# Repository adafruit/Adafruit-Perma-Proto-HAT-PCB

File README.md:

# Adafruit Perma-Proto HAT for Raspberry Pi Computers

&nbsp; <br />
Click to purchase from the Adafruit Shop:
- [With EEPROM](https://www.adafruit.com/product/2314)
- [Without EEPROM](https://www.adafruit.com/product/2310)

PCB files for the Adafruit Perma-Proto HAT for Raspberry Pi Computers (all with the 40 pin header)

Design your own Pi HAT, attach custom circuitry and otherwise dress your Pi Zero, A+, B+, Pi 2 or Pi 3 (any Pi with a 2x20 connector) with this jaunty prototyping HAT kit.

To kick off the Adafruit HAT party, we have this Perma-Proto inspired plug in daughter board. It has a grid of 0.1" prototyping soldering holes for attaching chips, resistors, LED, potentiometers and more. The holes are connected underneath with traces to mimic the solderless breadboards with which you're familiar. There's also long power strips for +3V, +5V and Ground connections to the Pi. Near the top we break out nearly every pin you could want to connect to the Pi (#26 didn't quite make the cut).

This is just the basic version of our Perma-Proto HAT.  It comes with a printed circuit board and a single 2x20 GPIO Header for Raspberry Pi to put your Perma-Proto on top of your Raspberry Pi (like a nice little hat...) This version does not come with an EEPROM so you can 'stack' it with other HATs without worrying about an EEPROM address collision.

Format is EagleCAD schematic and board layout

For more details, check out the product pages at

-----> https://www.adafruit.com/products/2310

-----> https://www.adafruit.com/products/2314

### License

Adafruit invests time and resources providing this open source design, please support Adafruit and open-source hardware by [purchasing products from Adafruit](https://www.adafruit.com)!

All text above must be included in any redistribution

Designed by Limor Fried/Ladyada for Adafruit Industries.
Creative Commons Attribution/Share-Alike, all text above must be included in any redistribution 
See license.txt for additional information.

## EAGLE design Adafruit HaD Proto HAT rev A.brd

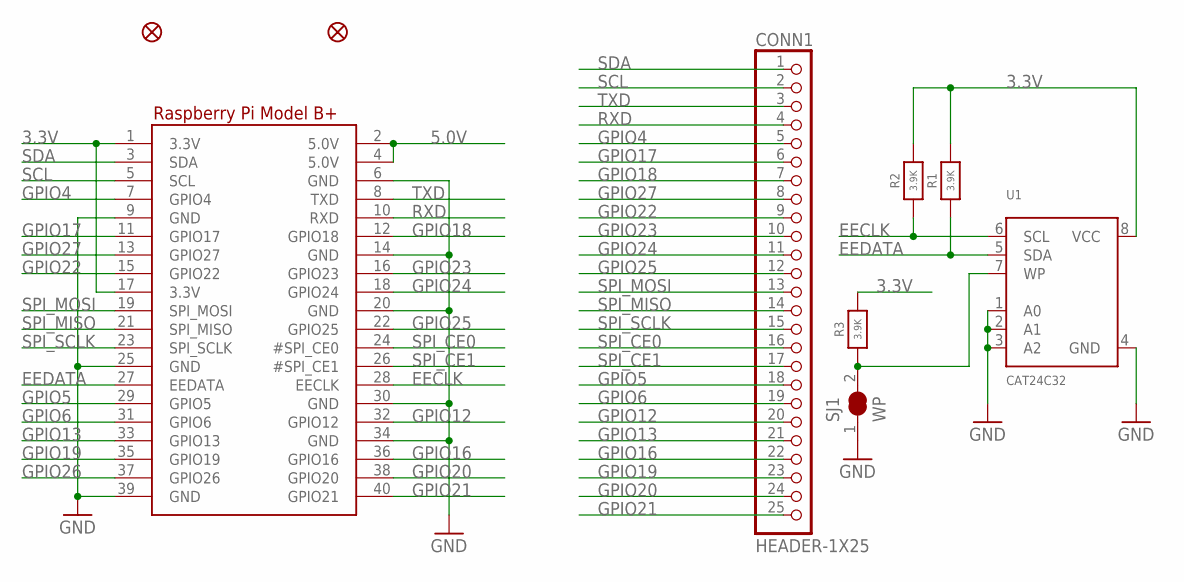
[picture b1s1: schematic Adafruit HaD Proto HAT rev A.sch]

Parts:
CONN1: HEADER-1X25; 1X25_ROUND_70MIL
FID2, FID3: FIDUCIAL""; FIDUCIAL_1MM
R1, R2, R3: 3.9K; 0805-NO
RPI1: RASPBERRYPI_BPLUS_HATNOSLOTS; PI_HAT_NOSLOTS
SJ1: WP; SOLDERJUMPER_CLOSEDWIRE
U1: CAT24C32; SOIC8_150MIL

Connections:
3.3V: R1.2, R2.2, R3.2, RPI1.1 (3.3V), RPI1.17 (3.3V), U1.8 (VCC)
5.0V: RPI1.2 (5.0V), RPI1.4 (5.0V)
EECLK: R2.1, RPI1.28 (EECLK), U1.6 (SCL)
EEDATA: R1.1, RPI1.27 (EEDATA), U1.5 (SDA)
GND: RPI1.6 (GND), RPI1.9 (GND), RPI1.14 (GND), RPI1.20 (GND), RPI1.25 (GND), RPI1.30 (GND), RPI1.34 (GND), RPI1.39 (GND), SJ1.1, U1.1 (A0), U1.2 (A1), U1.3 (A2), U1.4 (GND)
GPIO4: CONN1.5, RPI1.7 (GPIO4)
GPIO5: CONN1.18, RPI1.29 (GPIO5)
GPIO6: CONN1.19, RPI1.31 (GPIO6)
GPIO12: CONN1.20, RPI1.32 (GPIO12)
GPIO13: CONN1.21, RPI1.33 (GPIO13)
GPIO16: CONN1.22, RPI1.36 (GPIO16)
GPIO17: CONN1.6, RPI1.11 (GPIO17)
GPIO18: CONN1.7, RPI1.12 (GPIO18)
GPIO19: CONN1.23, RPI1.35 (GPIO19)
GPIO20: CONN1.24, RPI1.38 (GPIO20)
GPIO21: CONN1.25, RPI1.40 (GPIO21)
GPIO22: CONN1.9, RPI1.15 (GPIO22)
GPIO23: CONN1.10, RPI1.16 (GPIO23)
GPIO24: CONN1.11, RPI1.18 (GPIO24)
GPIO25: CONN1.12, RPI1.22 (GPIO25)
GPIO26: RPI1.37 (GPIO26)
GPIO27: CONN1.8, RPI1.13 (GPIO27)
unnamed: R3.1, SJ1.2, U1.7 (WP)
RXD: CONN1.4, RPI1.10 (RXD)
SCL: CONN1.2, RPI1.5 (SCL)
SDA: CONN1.1, RPI1.3 (SDA)
SPI_CE0: CONN1.16, RPI1.24 (#SPI_CE0)
SPI_CE1: CONN1.17, RPI1.26 (#SPI_CE1)
SPI_MISO: CONN1.14, RPI1.21 (SPI_MISO)
SPI_MOSI: CONN1.13, RPI1.19 (SPI_MOSI)
SPI_SCLK: CONN1.15, RPI1.23 (SPI_SCLK)
TXD: CONN1.3, RPI1.8 (TXD)

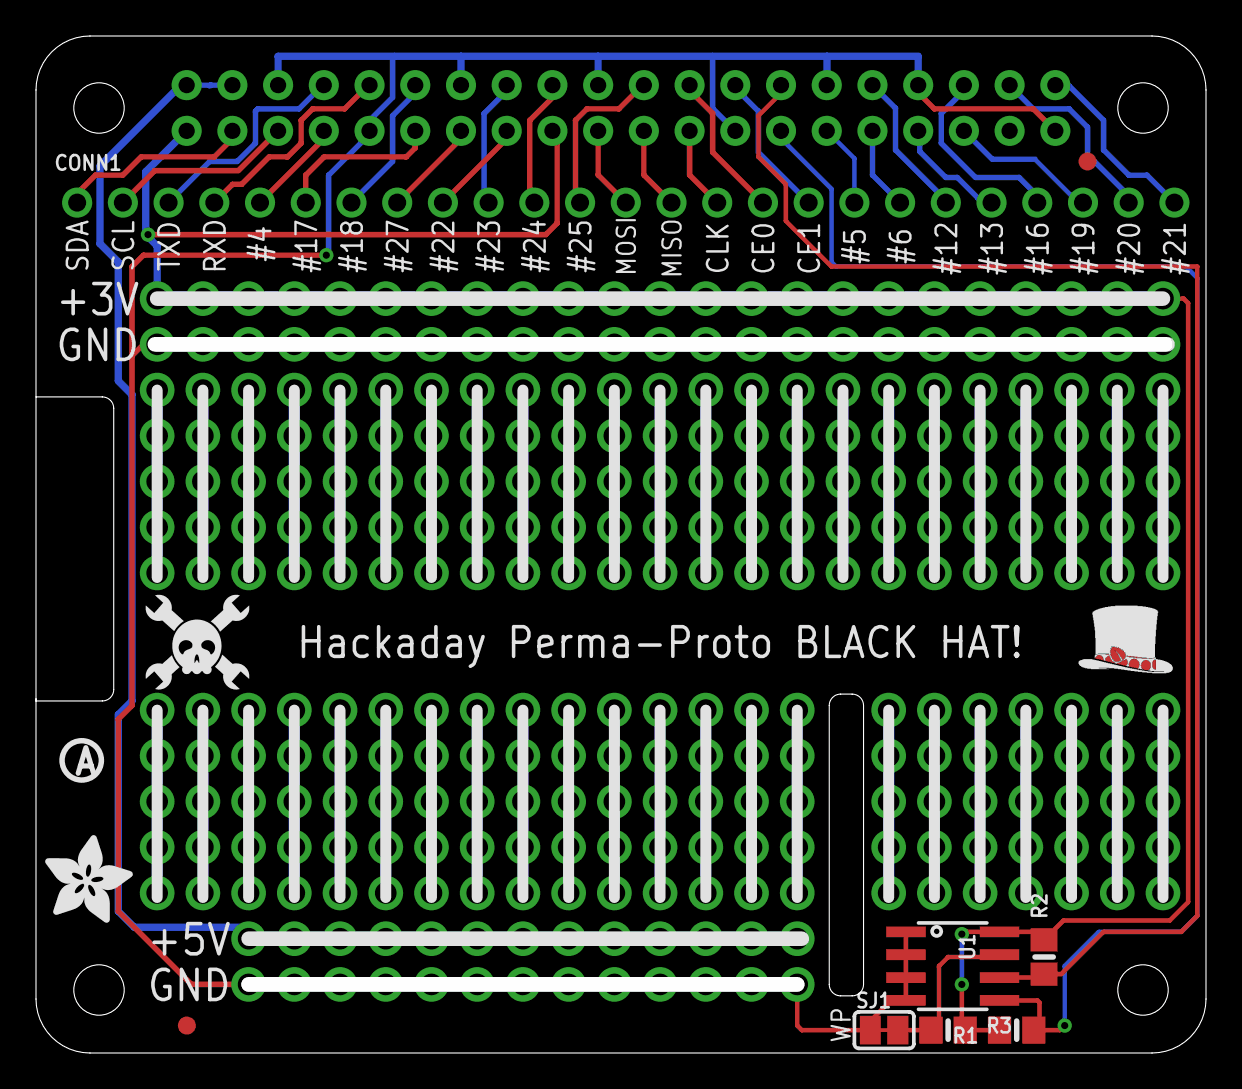
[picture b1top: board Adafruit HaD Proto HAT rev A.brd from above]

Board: 2 copper layers, 65.0 x 56.5 mm, 13 parts (0 on the bottom side), 31 nets.

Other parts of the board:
U$1: ADAFRUIT_5MM
U$2: PIHATLOGO
U$3: PCBFEAT-REV-056
U$5: HAD_LOGO_200MIL

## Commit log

2015-02-05 init
2015-02-05 tired
2019-05-16 Add images

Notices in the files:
parts and their libraries:
microbuilder: This work is placed in the public domain, and may be freely used for commercial and non-commercial work with the following conditions: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
